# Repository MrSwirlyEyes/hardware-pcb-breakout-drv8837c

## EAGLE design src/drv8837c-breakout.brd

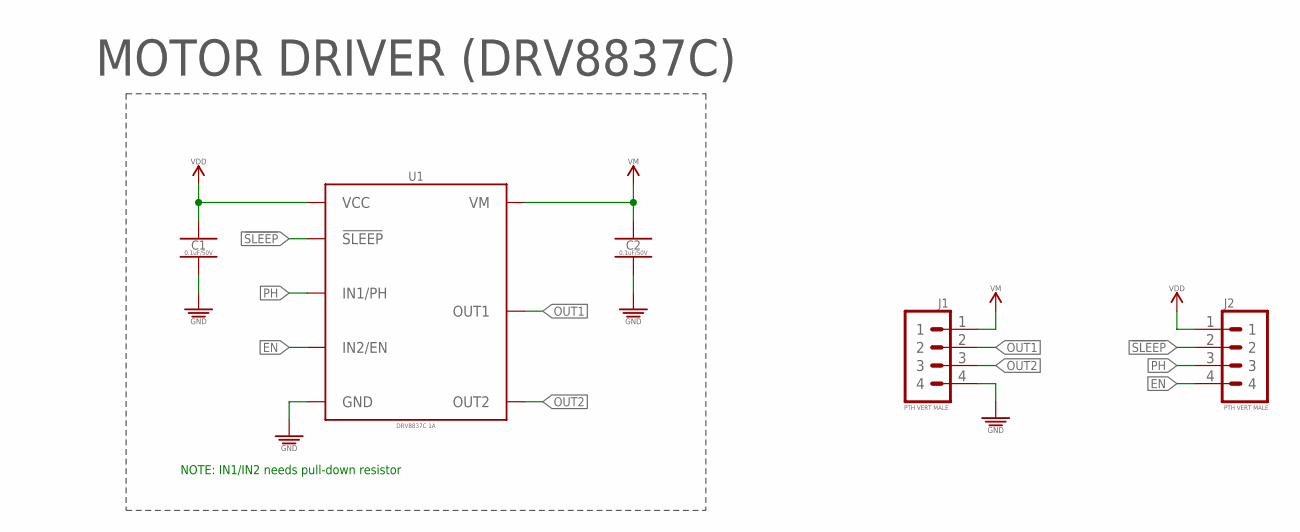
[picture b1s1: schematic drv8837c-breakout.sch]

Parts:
C1, C2: 0.1uF/50V; CAPC1005X55_SMD-0402
J1, J2: PTH VERT MALE; HDRV4W64P254_1X4_1016X254X838B
U1: DRV8837C 1A; WSON-8-PPAD

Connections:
!SLEEP!: J2.2, U1.7 (!SLEEP!)
EN: J2.4, U1.5 (IN2/EN)
GND: C1.2, C2.2, J1.4, U1.4 (GND), U1.GND, U1.P$1 (GND), U1.P$2 (GND)
OUT1: J1.2, U1.2 (OUT1)
OUT2: J1.3, U1.3 (OUT2)
PH: J2.3, U1.6 (IN1/PH)
VDD: C1.1, J2.1, U1.8 (VCC)
VM: C2.1, J1.1, U1.1 (VM)

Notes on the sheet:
MOTOR DRIVER (DRV8837C)
NOTE: IN1/IN2 needs pull-down resistor

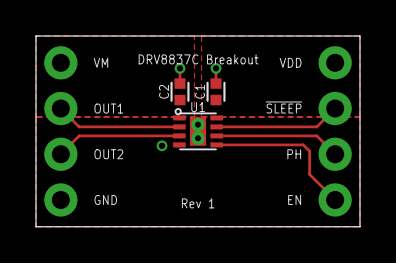
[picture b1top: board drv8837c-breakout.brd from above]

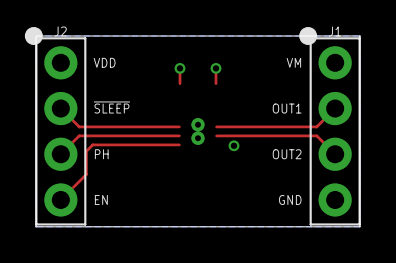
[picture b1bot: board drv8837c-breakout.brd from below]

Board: 2 copper layers, 18.0 x 10.6 mm, 5 parts (2 on the bottom side), 8 nets.

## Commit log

2021-08-11 Initialize repo.
